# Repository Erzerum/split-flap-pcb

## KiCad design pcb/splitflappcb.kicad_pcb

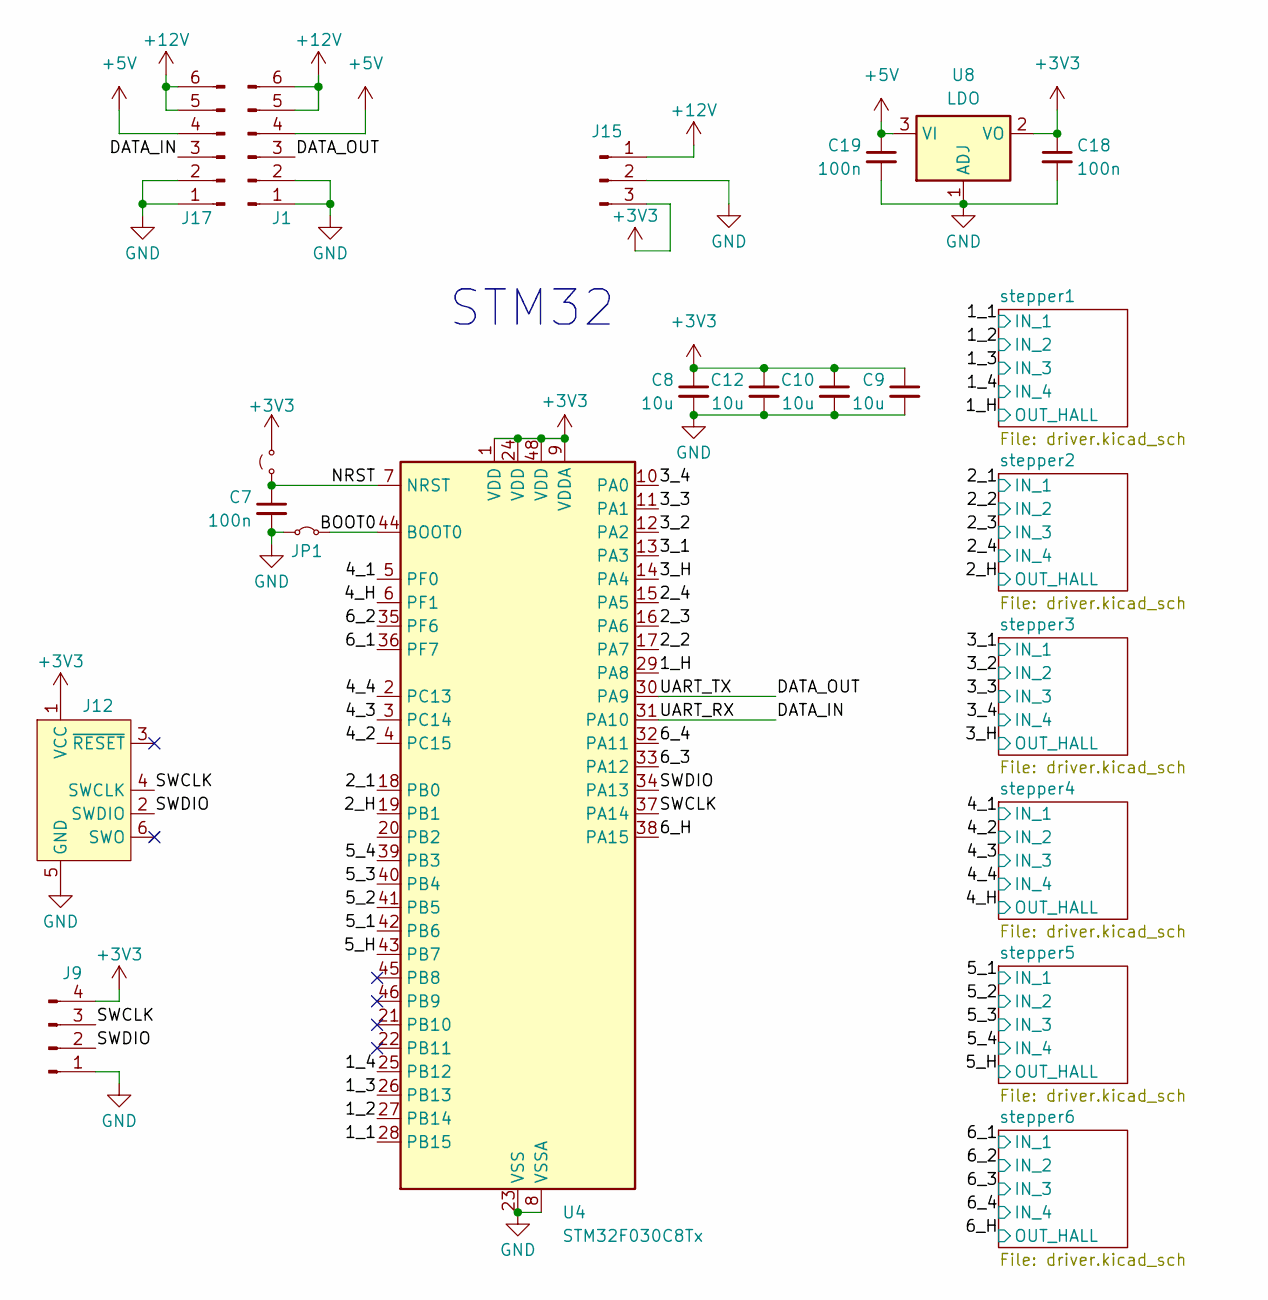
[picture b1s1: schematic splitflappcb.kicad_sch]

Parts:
C7, C18, C19: 100n; C_0603_1608Metric; LCSC C14663
C8, C9, C10, C12: 10u; C_0603_1608Metric; LCSC C19702
J1, J17: Conn_01x04_Pin; JST_XH_B6B-XH-AM_1x06_P2.50mm_Vertical; LCSC C161873
J9: Conn_01x04_Pin; PinHeader_1x04_P2.54mm_Vertical; LCSC C6332197
J12: Conn_ARM_SWD_TagConnect_TC2030-NL; Tag-Connect_TC2030-IDC-NL_2x03_P1.27mm_Vertical
J15: SOT-89-3; LCSC C351450
JP1: Jumper_2_Small_Bridged; SolderJumper-2_P1.3mm_Bridged_RoundedPad1.0x1.5mm
JP2: Jumper_2_Small_Open; SolderJumper-2_P1.3mm_Open_RoundedPad1.0x1.5mm
U4: STM32F030C8Tx; LQFP-48_7x7mm_P0.5mm; LCSC C62514
U8: LDO; SOT-23-3; LCSC C5446

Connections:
+3V3: C8.1, C9.1, C10.1, C12.1, C18.1, J9.4, J12.1 (VCC), J15.3, JP2.2 (B), U4.1 (VDD), U4.9 (VDDA), U4.24 (VDD), U4.48 (VDD), U8.2 (VO)
+5V: C19.1, J1.4, J17.4, U8.3 (VI); also elsewhere on the board
+12V: J1.5, J1.6, J15.1, J17.5, J17.6; also elsewhere on the board
/1_1: U4.28 (PB15); also elsewhere on the board
/1_2: U4.27 (PB14); also elsewhere on the board
/1_3: U4.26 (PB13); also elsewhere on the board
/1_4: U4.25 (PB12); also elsewhere on the board
/1_H: U4.29 (PA8); also elsewhere on the board
/2_1: U4.18 (PB0); also elsewhere on the board
/2_2: U4.17 (PA7); also elsewhere on the board
/2_3: U4.16 (PA6); also elsewhere on the board
/2_4: U4.15 (PA5); also elsewhere on the board
/2_H: U4.19 (PB1); also elsewhere on the board
/3_1: U4.13 (PA3); also elsewhere on the board
/3_2: U4.12 (PA2); also elsewhere on the board
/3_3: U4.11 (PA1); also elsewhere on the board
/3_4: U4.10 (PA0); also elsewhere on the board
/3_H: U4.14 (PA4); also elsewhere on the board
/4_1: U4.5 (PF0); also elsewhere on the board
/4_2: U4.4 (PC15); also elsewhere on the board
/4_3: U4.3 (PC14); also elsewhere on the board
/4_4: U4.2 (PC13); also elsewhere on the board
/4_H: U4.6 (PF1); also elsewhere on the board
/5_1: U4.42 (PB6); also elsewhere on the board
/5_2: U4.41 (PB5); also elsewhere on the board
/5_3: U4.40 (PB4); also elsewhere on the board
/5_4: U4.39 (PB3); also elsewhere on the board
/5_H: U4.43 (PB7); also elsewhere on the board
/6_1: U4.36 (PF7); also elsewhere on the board
/6_2: U4.35 (PF6); also elsewhere on the board
/6_3: U4.33 (PA12); also elsewhere on the board
/6_4: U4.32 (PA11); also elsewhere on the board
/6_H: U4.38 (PA15); also elsewhere on the board
/BOOT0: JP1.1 (A), U4.44 (BOOT0)
/DATA_IN: J17.3, U4.31 (PA10)
/DATA_OUT: J1.3, U4.30 (PA9)
/NRST: C7.1, JP2.1 (A), U4.7 (NRST)
/SWCLK: J9.3, J12.4 (SWCLK), U4.37 (PA14)
/SWDIO: J9.2, J12.2 (SWDIO), U4.34 (PA13)
GND: C7.2, C8.2, C9.2, C10.2, C12.2, C18.2, C19.2, J1.1, J1.2, J9.1, J12.5 (GND), J15.2, J17.1, J17.2, JP1.2 (B), U4.8 (VSSA), U4.23 (VSS), U4.47 (VSS), U8.1 (ADJ); also elsewhere on the board

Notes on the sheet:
STM32

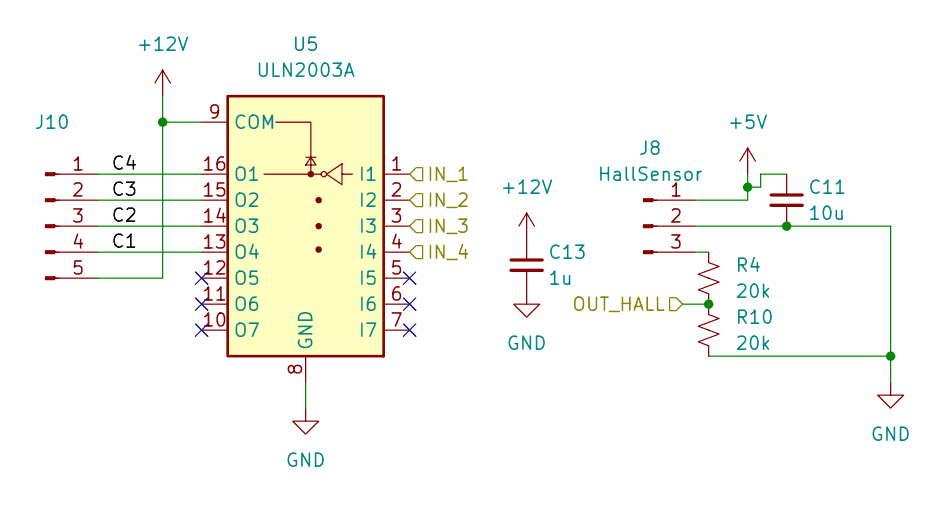
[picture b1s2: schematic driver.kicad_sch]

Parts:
C11: 10u; C_0603_1608Metric; LCSC C19702
C13: 1u; C_0603_1608Metric; LCSC C15849
J8: HallSensor; PinHeader_1x03_P2.54mm_Vertical; LCSC C6332196
J10: Conn_01x05_Pin; JST_XH_B5B-XH-AM_1x05_P2.50mm_Vertical; LCSC C161872
R4, R10: 20k; R_0805_2012Metric; LCSC C4328
U5: ULN2003A; SOIC-16_3.9x9.9mm_P1.27mm; LCSC C7512

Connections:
+5V: C11.1, J8.1; also elsewhere on the board
+12V: C13.1, J10.5, U5.9 (COM); also elsewhere on the board
/4_1: U5.1 (I1); also elsewhere on the board
/4_2: U5.2 (I2); also elsewhere on the board
/4_3: U5.3 (I3); also elsewhere on the board
/4_4: U5.4 (I4); also elsewhere on the board
/4_H: R4.2, R10.1; also elsewhere on the board
/stepper4/C1: J10.4, U5.13 (O4)
/stepper4/C2: J10.3, U5.14 (O3)
/stepper4/C3: J10.2, U5.15 (O2)
/stepper4/C4: J10.1, U5.16 (O1)
GND: C11.2, C13.2, J8.2, R10.2, U5.8 (GND); also elsewhere on the board
unnamed: J8.3, R4.1

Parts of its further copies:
C1, C3, C5, C14, C16: 10u; C_0603_1608Metric; LCSC C19702
C2, C4, C6, C15, C17: 1u; C_0603_1608Metric; LCSC C15849
J2, J5, J6, J11, J14: HallSensor; PinHeader_1x03_P2.54mm_Vertical; LCSC C6332196
J3, J4, J7, J13, J16: Conn_01x05_Pin; JST_XH_B5B-XH-AM_1x05_P2.50mm_Vertical; LCSC C161872
R1, R2, R3, R5, R6, R7, R8, R9, R11, R12: 20k; R_0805_2012Metric; LCSC C4328
U1, U2, U3, U6, U7: ULN2003A; SOIC-16_3.9x9.9mm_P1.27mm; LCSC C7512

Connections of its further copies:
+5V: C1.1, C3.1, C5.1, C14.1, C16.1, J2.1, J5.1, J6.1, J11.1, J14.1; also elsewhere on the board
+12V: C2.1, C4.1, C6.1, C15.1, C17.1, J3.5, J4.5, J7.5, J13.5, J16.5, U1.9 (COM), U2.9 (COM), U3.9 (COM), U6.9 (COM), U7.9 (COM); also elsewhere on the board
/1_1: U1.1 (I1); also elsewhere on the board
/1_2: U1.2 (I2); also elsewhere on the board
/1_3: U1.3 (I3); also elsewhere on the board
/1_4: U1.4 (I4); also elsewhere on the board
/1_H: R1.2, R7.1; also elsewhere on the board
/2_1: U2.1 (I1); also elsewhere on the board
/2_2: U2.2 (I2); also elsewhere on the board
/2_3: U2.3 (I3); also elsewhere on the board
/2_4: U2.4 (I4); also elsewhere on the board
/2_H: R2.2, R8.1; also elsewhere on the board
/3_1: U3.1 (I1); also elsewhere on the board
/3_2: U3.2 (I2); also elsewhere on the board
/3_3: U3.3 (I3); also elsewhere on the board
/3_4: U3.4 (I4); also elsewhere on the board
/3_H: R3.2, R9.1; also elsewhere on the board
/5_1: U6.1 (I1); also elsewhere on the board
/5_2: U6.2 (I2); also elsewhere on the board
/5_3: U6.3 (I3); also elsewhere on the board
/5_4: U6.4 (I4); also elsewhere on the board
/5_H: R5.2, R11.1; also elsewhere on the board
/6_1: U7.1 (I1); also elsewhere on the board
/6_2: U7.2 (I2); also elsewhere on the board
/6_3: U7.3 (I3); also elsewhere on the board
/6_4: U7.4 (I4); also elsewhere on the board
/6_H: R6.2, R12.1; also elsewhere on the board
/stepper1/C1: J3.4, U1.13 (O4)
/stepper1/C2: J3.3, U1.14 (O3)
/stepper1/C3: J3.2, U1.15 (O2)
/stepper1/C4: J3.1, U1.16 (O1)
/stepper2/C1: J4.4, U2.13 (O4)
/stepper2/C2: J4.3, U2.14 (O3)
/stepper2/C3: J4.2, U2.15 (O2)
/stepper2/C4: J4.1, U2.16 (O1)
/stepper3/C1: J7.4, U3.13 (O4)
/stepper3/C2: J7.3, U3.14 (O3)
/stepper3/C3: J7.2, U3.15 (O2)
/stepper3/C4: J7.1, U3.16 (O1)
/stepper5/C1: J13.4, U6.13 (O4)
/stepper5/C2: J13.3, U6.14 (O3)
/stepper5/C3: J13.2, U6.15 (O2)
/stepper5/C4: J13.1, U6.16 (O1)
/stepper6/C1: J16.4, U7.13 (O4)
/stepper6/C2: J16.3, U7.14 (O3)
/stepper6/C3: J16.2, U7.15 (O2)
/stepper6/C4: J16.1, U7.16 (O1)
GND: C1.2, C2.2, C3.2, C4.2, C5.2, C6.2, C14.2, C15.2, C16.2, C17.2, J2.2, J5.2, J6.2, J11.2, J14.2, R7.2, R8.2, R9.2, R11.2, R12.2, U1.8 (GND), U2.8 (GND), U3.8 (GND), U6.8 (GND), U7.8 (GND); also elsewhere on the board
unnamed: J2.3, R1.1
unnamed: J5.3, R2.1
unnamed: J6.3, R3.1
unnamed: J11.3, R5.1
unnamed: J14.3, R6.1

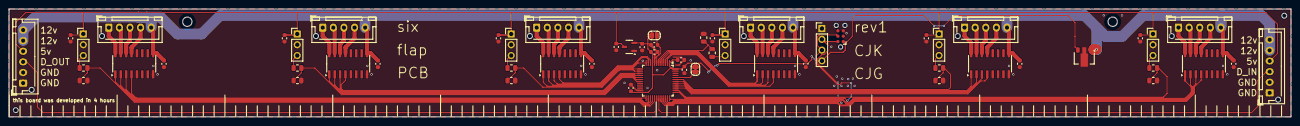
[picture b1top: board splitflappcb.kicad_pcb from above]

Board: 2 copper layers, 302.0 x 25.4 mm, 58 parts (0 on the bottom side), 70 nets.

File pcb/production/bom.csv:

Designator,Footprint,Quantity,Value,LCSC Part #
"C1, C10, C11, C12, C14, C16, C3, C5, C8, C9",0603,10,10u,C19702
"C13, C15, C17, C2, C4, C6",0603,6,1u,C15849
"C18, C19, C7",0603,3,100n,C14663
"J1, J17",JST_XH_B6B-XH-AM_1x06_P2.50mm_Vertical,2,Conn_01x04_Pin,C161873
"J10, J13, J16, J3, J4, J7",JST_XH_B5B-XH-AM_1x05_P2.50mm_Vertical,6,Conn_01x05_Pin,C161872
"J11, J14, J2, J5, J6, J8",PinHeader_1x03_P2.54mm_Vertical,6,HallSensor,C6332196
J15,SOT-89-3,1,~,C351450
J9,PinHeader_1x04_P2.54mm_Vertical,1,Conn_01x04_Pin,C6332197
"R1, R10, R11, R12, R2, R3, R4, R5, R6, R7, R8, R9",0805,12,20k,C4328
"U1, U2, U3, U5, U6, U7",SOIC-16_3.9x9.9mm_P1.27mm,6,ULN2003A,C7512
U4,LQFP-48_7x7mm_P0.5mm,1,STM32F030C8Tx,C62514
U8,SOT-23-3,1,LDO,C5446

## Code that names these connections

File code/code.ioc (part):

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Mcu.Name=STM32F030C8Tx
Mcu.Package=LQFP48
Mcu.UserName=STM32F030C8Tx
PA0.Signal=GPIO_Output
PA1.Signal=GPIO_Output
PA10.Mode=Asynchronous
PA10.Signal=USART1_RX
PA11.Signal=GPIO_Output
PA12.Signal=GPIO_Output
PA13.Mode=Serial_Wire
PA13.Signal=SYS_SWDIO
PA14.Mode=Serial_Wire
PA14.Signal=SYS_SWCLK
PA15.Signal=GPIO_Input
PA2.Signal=GPIO_Output
PA3.Signal=GPIO_Output
PA4.Signal=GPIO_Input
PA5.Signal=GPIO_Output
PA6.Signal=GPIO_Output
PA7.Signal=GPIO_Output
PA8.Signal=GPIO_Input
PA9.Mode=Asynchronous
PA9.Signal=USART1_TX
PB0.Signal=GPIO_Output
PB1.Signal=GPIO_Input
PB12.Signal=GPIO_Output
PB13.Signal=GPIO_Output
PB14.Signal=GPIO_Output
PB15.Signal=GPIO_Output
PB3.Signal=GPIO_Output
PB4.Signal=GPIO_Output
PB5.Signal=GPIO_Output
PB6.Signal=GPIO_Output
PB7.Signal=GPIO_Input
PC13.Signal=GPIO_Output
PC14-OSC32_IN.Signal=GPIO_Output
PC15-OSC32_OUT.Signal=GPIO_Output
PF0-OSC_IN.Signal=GPIO_Output
PF1-OSC_OUT.Signal=GPIO_Input
PF6.Signal=GPIO_Output
PF7.Signal=GPIO_Output
RCC.SYSCLKFreq_VALUE=48000000
RCC.SYSCLKSource=RCC_SYSCLKSOURCE_PLLCLK
board=custom

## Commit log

2024-05-23 how many attempts does it take
    me when i try to use git
2024-05-27 Changed out a tantalum capacitor for four better ones
2024-05-27 Fixed several drc errors
    also slightly adjusted some of the silkscreen
2024-07-14 ordered rev1
2024-07-21 moved everything into PCB folder
2024-07-21 started cubemx code
2024-07-21 trying to convert to LF
2024-07-21 started code!
2024-07-21 code spins all the motors, changed pcb to black
2024-07-25 acceleration sorta
2024-08-31 S E N T
2024-08-31 ordered ol
